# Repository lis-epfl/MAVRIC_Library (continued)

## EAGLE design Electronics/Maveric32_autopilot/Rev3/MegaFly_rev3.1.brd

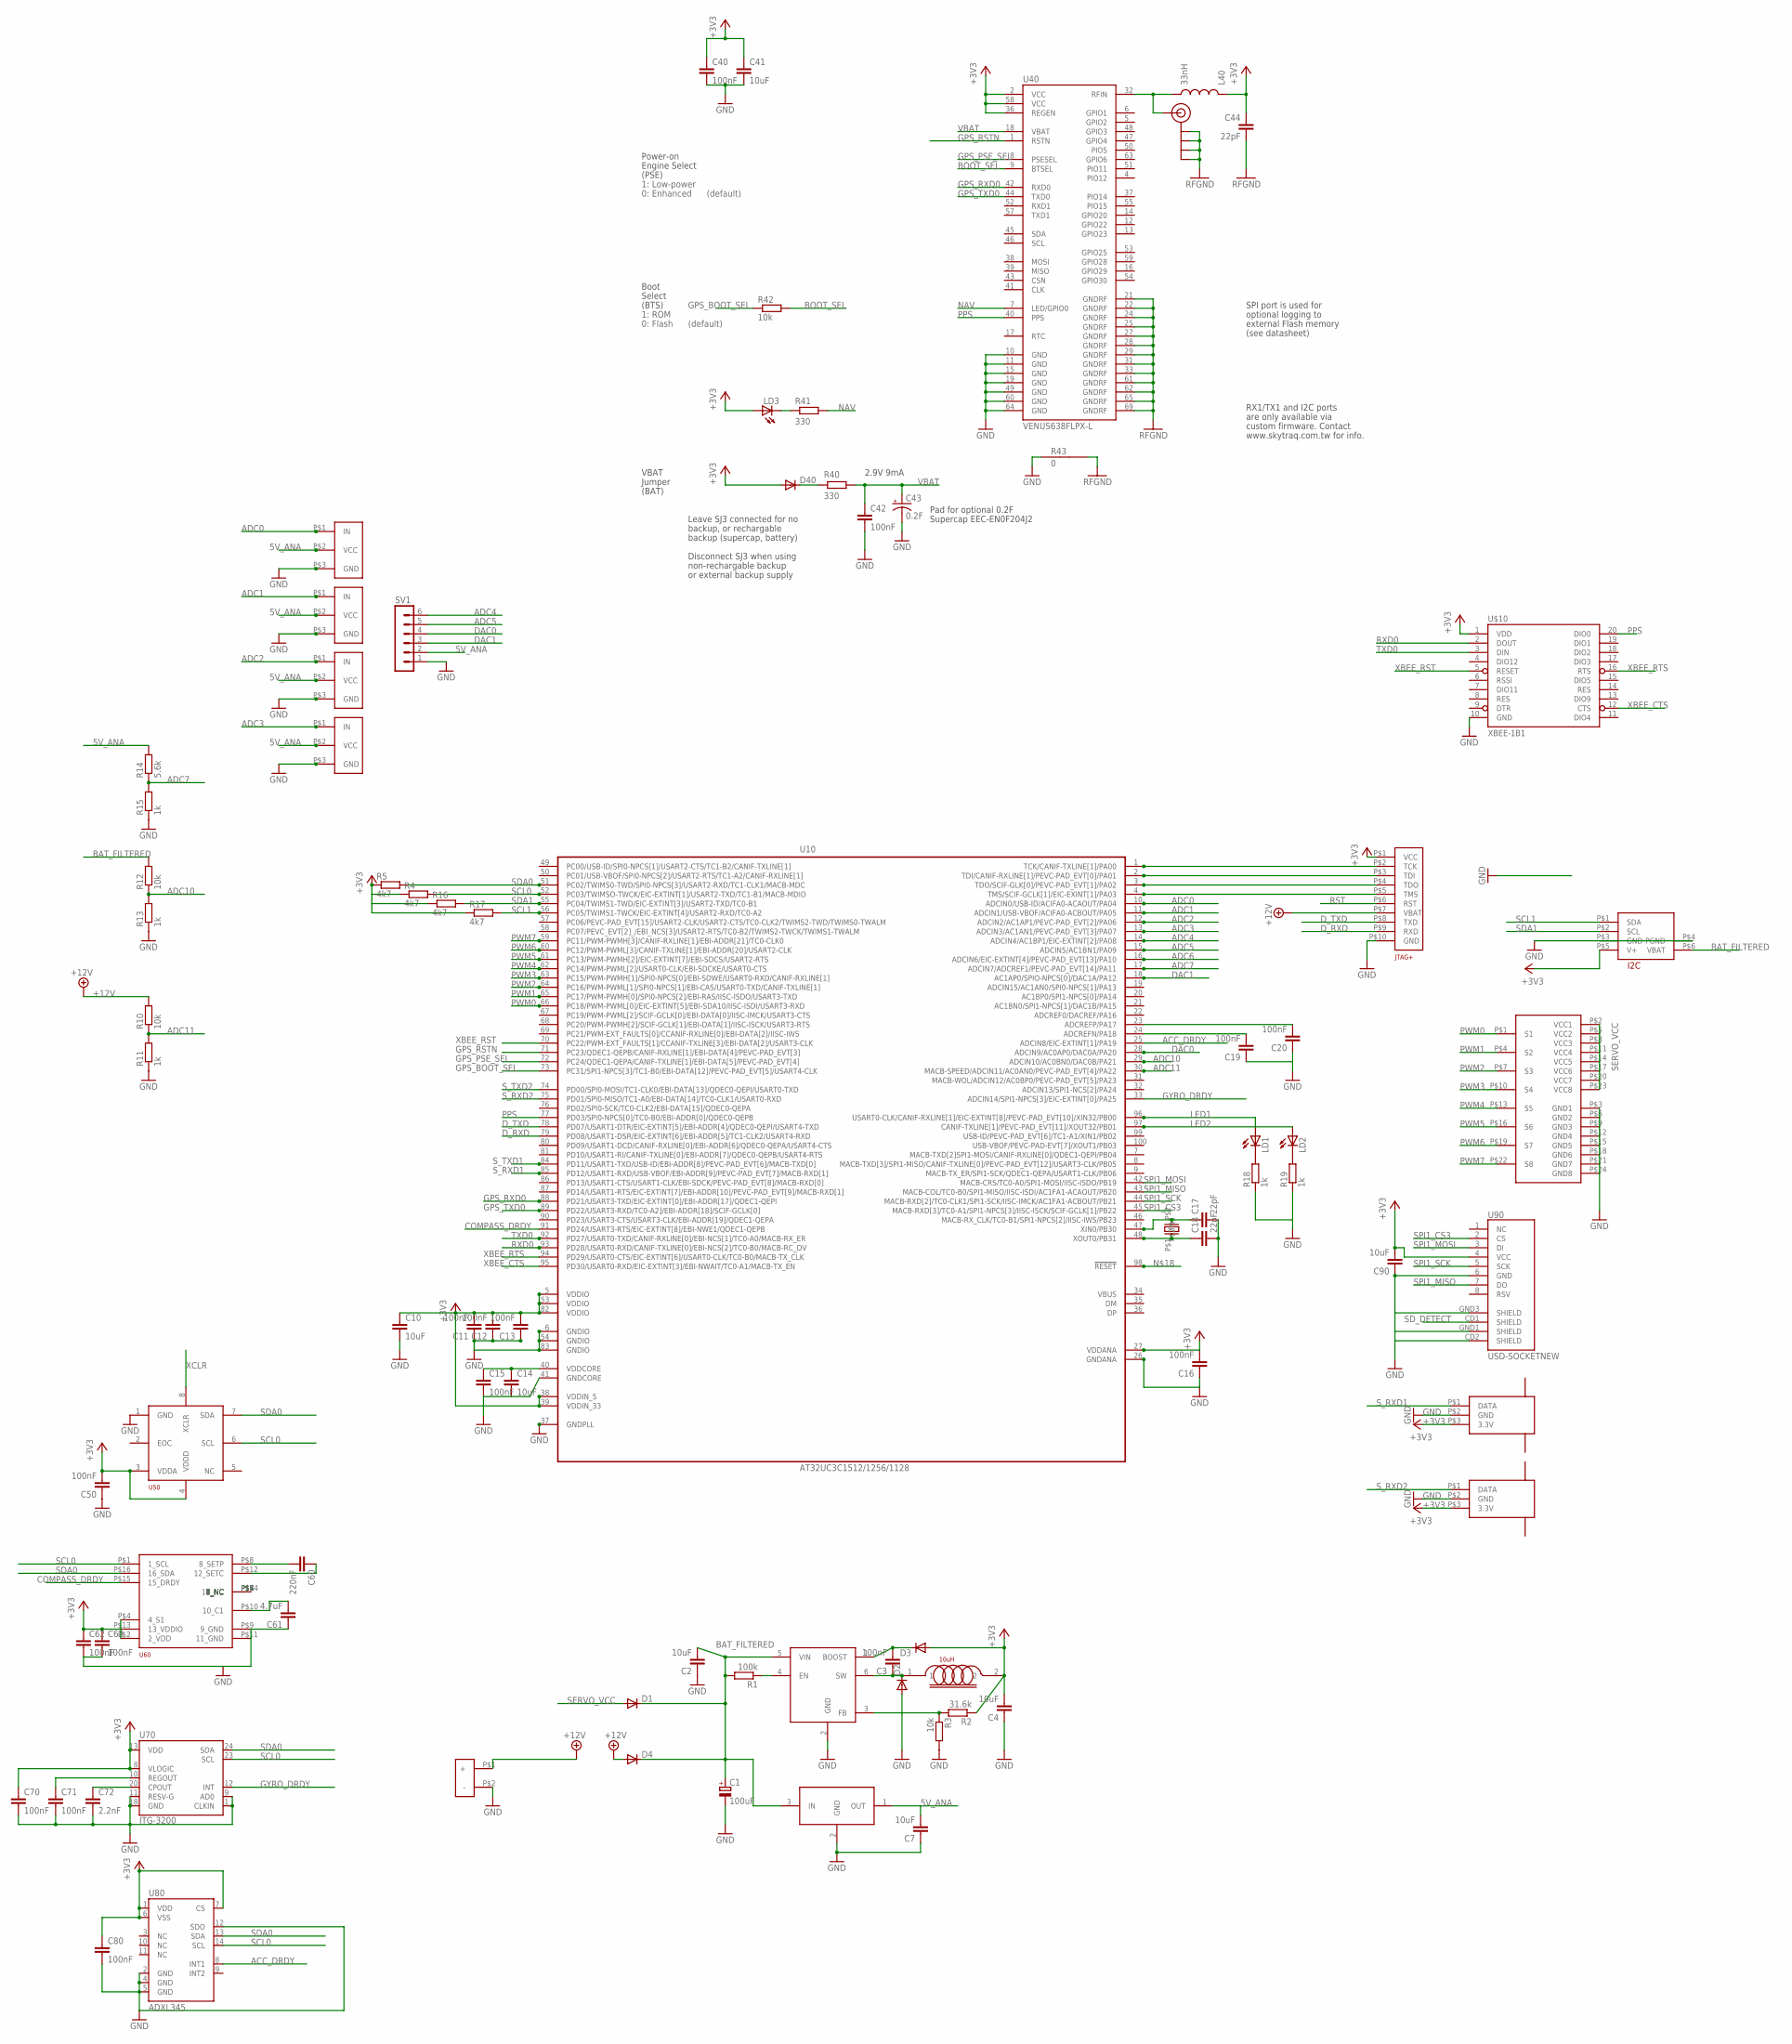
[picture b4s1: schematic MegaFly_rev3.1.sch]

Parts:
C1: 100uF; D/7343-31R
C2, C4, C7, C10, C14, C41, C90: 10uF; C0805
C3, C11, C12, C13, C15, C16, C19, C20, C40, C42, C50, C62, C63, C70, C71, C80: 100nF; C0603
C17, C18, C44: 22pF; C0402
C43: 0.2F; EN_J2
C60: 220nF; C0805
C61: 4.7uF; C0805
C72: 2.2nF; C0603
D1, D2, D3, D4, D40: DIODESOD; SOD-323
JP5: SMA_EDGE; SMA-EDGE
L1: 10uH; C1210
L40: 33nH; 0603
LD1, LD2, LD3: LEDCHIPLED_0805; CHIPLED_0805
R1: 100k; R0603
R2: 31.6k; R0603
R3, R10, R12, R42: 10k; R0603
R4, R5, R16, R17: 4k7; R0603
R11, R13, R15, R18, R19: 1k; R0603
R14: 5.6k; R0603
R40, R41: 330; R0603
R43: 0; GND-JUMP
SV1: MA06-1
U1: LM2734; SOT23-6
U2: LDO_3PINSOT89_MC78LXX; SOT89
U10: AT32UC3C1512/1256/1128; TQFP100
U40: VENUS638FLPX-L; VENUS638FLPX
U50: BMP085
U60: HMC5883L; LPCC16_0.5MM
U70: ITG-3200; QFN-24
U80: ADXL345; LGA14
U90: USD-SOCKETNEW; MICRO-SD-SOCKET-PP
U$1: AVR32_JTAG+SERIAL; MOLEX_CONNECTOR_10PINS
U$3: SERVOCONNECTOR_X8STANDARD; HEADER3X8
U$8: CRYSTAL; SMD_CRYSTAL_ABM
U$9: POWER
U$10: XBEE-1B1; XBEE-1
U$11, U$12: SPEKTRUM_RECEIVER; JST_1.5MM_3WAY
U$13, U$15, U$16, U$17: SENSOR; SERVO_COMPACT
U$18: I2C-BUS; I2C-HEADER

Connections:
5V_ANA: C7.2, R14.2, SV1.2, U2.1 (OUT), U$13.P$2 (VCC), U$15.P$2 (VCC), U$16.P$2 (VCC), U$17.P$2 (VCC)
+3V3: C4.2, C10.1, C11.2, C12.2, C13.2, C16.2, C40.1, C41.1, C44.1, C50.2, C62.1, C63.1, C70.1, C80.1, C90.2, D3.2 (A), D40.2 (A), L1.2, L40.1, LD3.A, R2.1, R4.1, R5.1, R16.1, R17.1, U10.5 (VDDIO), U10.27 (VDDANA), U10.38 (VDDIN_5), U10.39 (VDDIN_33), U10.53 (VDDIO), U10.82 (VDDIO), U40.2 (VCC), U40.36 (REGEN), U40.58 (VCC), U50.3 (VDDA), U50.4 (VDDD), U60.P$2 (2_VDD), U60.P$4 (4_S1), U60.P$13 (13_VDDIO), U70.8 (VLOGIC), U70.13 (VDD), U80.1 (VDD), U80.6 (VSS), U80.7 (CS), U90.4 (VCC), U$1.P$1 (VCC), U$10.1 (VDD), U$11.P$3 (3.3V), U$12.P$3 (3.3V), U$18.P$5 (V+)
+12V: D4.2 (A), R10.2, U$1.P$7 (VBAT), U$9.P$1 (+)
ACC_DRDY: U80.8 (INT1)
ADC0: U10.10 (ADCIN0/USB-ID/ACIFA0-ACAOUT/PA04), U$17.P$1 (IN)
ADC1: U10.11 (ADCIN1/USB-VBOF/ACIFA0-ACBOUT/PA05), U$16.P$1 (IN)
ADC2: U10.12 (ADCIN2/AC1AP1/PEVC-PAD_EVT[2]/PA06), U$13.P$1 (IN)
ADC3: U10.13 (ADCIN3/AC1AN1/PEVC-PAD_EVT[3]/PA07), U$15.P$1 (IN)
ADC4: SV1.6, U10.14 (ADCIN4/AC1BP1/EIC-EXTINT[2]/PA08)
ADC5: SV1.5, U10.15 (ADCIN5/AC1BN1/PA09)
ADC6: U10.16 (ADCIN6/EIC-EXTINT[4]/PEVC-PAD_EVT[13]/P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)
ADC7: R14.1, R15.2, U10.17 (ADCIN7/ADCREF1/PEVC-PAD_EVT[14]/PA11)
ADC10: R12.1, R13.2, U10.29 (ADCIN10/AC0BN0/DAC0B/PA21)
ADC11: R10.1, R11.2, U10.30 (MACB-SPEED/ADCIN11/AC0AN0/PEVC-PAD_EVT[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)
ANT: JP5.SIG (SIGNAL), L40.2, U40.32 (RFIN)
BAT_FILTERED: C1.+, C2.2, D1.1 (C), D4.1 (C), R1.2, R12.2, U1.5 (VIN), U2.3 (IN), U$18.P$6 (VBAT)
BOOT_SEL: R42.2, U40.9 (BTSEL)
COMPASS_DRDY: U60.P$15 (15_DRDY)
DAC0: SV1.4, U10.28 (ADCIN9/AC0AP0/DAC0A/PA20)
DAC1: SV1.3, U10.18 (AC1AP0/SPIO-NPCS[0]/DAC1A/PA12)
D_RXD: U10.79 (PD08/USART1-DSR/EIC-EXTINT[6]/EBI-ADDR[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), U$1.P$9 (RXD)
D_TXD: U10.78 (PD07/USART1-DTR/EIC-EXTINT[5]/EBI-ADDR[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), U$1.P$8 (TXD)
GND: C1.-, C2.1, C4.1, C7.1, C10.2, C11.1, C12.1, C13.1, C14.2, C15.2, C16.1, C17.2, C18.2, C19.1, C20.1, C40.2, C41.2, C42.2, C43.-, C50.1, C61.1, C62.2, C63.2, C70.2, C71.2, C72.2, C80.2, C90.1, D2.2 (A), R3.2, R11.1, R13.1, R15.1, R18.1, R19.1, R43.1, SV1.1, U1.2 (GND), U2.2 (GND), U10.6 (GNDIO), U10.26 (GNDANA), U10.37 (GNDPLL), U10.41 (GNDCORE), U10.54 (GNDIO), U10.83 (GNDIO), U40.10 (GND), U40.11 (GND), U40.15 (GND), U40.19 (GND), U40.49 (GND), U40.60 (GND), U40.64 (GND), U50.1 (GND), U60.P$9 (9_GND), U60.P$11 (11_GND), U70.1 (CLKIN), U70.9 (AD0), U70.11 (RESV-G), U70.18 (GND), U80.2 (GND), U80.4 (GND), U80.5 (GND), U80.12 (SDO), U90.6 (GND), U90.CD2 (SHIELD), U90.GND1 (SHIELD), U90.GND3 (SHIELD), U$1.P$10 (GND), U$3.P$3 (GND1), U$3.P$6 (GND2), U$3.P$9 (GND3), U$3.P$12 (GND4), U$3.P$15 (GND5), U$3.P$18 (GND6), U$3.P$21 (GND7), U$3.P$24 (GND8), U$9.P$2 (-), U$10.10 (GND), U$11.P$2 (GND), U$12.P$2 (GND), U$13.P$3 (GND), U$15.P$3 (GND), U$16.P$3 (GND), U$17.P$3 (GND), U$18.P$3 (GND), U$18.P$4 (PGND)
GPS_BOOT_SEL: R42.1, U10.73 (PC31/SPI1-NPCS[3]/TC1-B0/EBI-DATA[12]/P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)
GPS_PSE_SEL: U10.72 (PC24/QDEC1-QEPA/CANIF-TXLINE[1]/EBI-DAT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), U40.8 (PSESEL)
GPS_RSTN: U10.71 (PC23/QDEC1-QEPB/CANIF-RXLINE[1]/EBI-DAT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), U40.1 (RSTN)
GPS_RXD0: U10.88 (PD21/USART3-TXD/EIC-EXTINT[0]/EBI-ADDR[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), U40.42 (RXD0)
GPS_TXD0: U10.89 (PD22/USART3-RXD/TC0-A2]/EBI-ADDR[18]/SC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), U40.44 (TXD0)
GYRO_DRDY: U70.12 (INT)
LED1: LD1.A, U10.96 (USART0-CLK/CANIF-RXLINE[1]/EIC-EXTINT[8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)
LED2: LD2.A, U10.97 (CANIF-TXLINE[1]/PEVC-PAD_EVT[11]/XOUT32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)
unnamed: U10.4 (TMS/SCIF-GCLK[1]/EIC-EXINT[1]/PA03), U$1.P$5 (TMS)
unnamed: U10.3 (TDO/SCIF-GLK[0]/PEVC-PAD_EVT[1]/PA02), U$1.P$4 (TDO)
unnamed: C18.1, U10.48 (XOUT0/PB31), U$8.P$1
unnamed: C17.1, U10.47 (XIN0/PB30), U$8.P$2
unnamed: LD1.C, R18.2
unnamed: R1.1, U1.4 (EN)
unnamed: LD2.C, R19.2
unnamed: C3.1, D2.1 (C), L1.1, U1.6 (SW)
unnamed: R2.2, R3.1, U1.3 (FB)
unnamed: C3.2, D3.1 (C), U1.1 (BOOST)
unnamed: C72.1, U70.20 (CPOUT)
unnamed: C61.2, U60.P$10 (10_C1)
unnamed: C60.2, U60.P$8 (8_SETP)
unnamed: C60.1, U60.P$12 (12_SETC)
unnamed: C71.1, U70.10 (REGOUT)
unnamed: LD3.C, R41.1
unnamed: U10.2 (TDI/CANIF-RXLINE[1]/PEVC-PAD_EVT[0]/PA01), U$1.P$3 (TDI)
unnamed: C14.1, C15.1, U10.40 (VDDCORE)
unnamed: D40.1 (C), R40.1
unnamed: U10.1 (TCK/CANIF-TXLINE[1]/PA00), U$1.P$2 (TCK)
unnamed: C19.2, U10.24 (ADCREFN/PA18)
unnamed: C20.2, U10.23 (ADCREFP/PA17)
NAV: R41.2, U40.7 (LED/GPIO0)
PPS: U10.77 (PD03/SPI0-NPCS[0]/TC0-B0/EBI-ADDR[0]/QD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), U40.40 (PPS), U$10.20 (DIO0)
PWM0: U10.66 (PC18/PWM-PWML[0]/EIC-EXTINT[5]/EBI-SDA1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), U$3.P$1 (S1)
PWM1: U10.65 (PC17/PWM-PWMH[0]/SPI0-NPCS[2]/EBI-RAS/I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), U$3.P$4 (S2)
PWM2: U10.64 (PC16/PWM-PWML[1]/SPI0-NPCS[1]/EBI-CAS/U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), U$3.P$7 (S3)
PWM3: U10.63 (PC15/PWM-PWMH[1]/SPI0-NPCS[0]/EBI-SDWE/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), U$3.P$10 (S4)
PWM4: U10.62 (PC14/PWM-PWML[2]/USART0-CLK/EBI-SDCKE/U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), U$3.P$13 (S5)
PWM5: U10.61 (PC13/PWM-PWMH[2]/EIC-EXTINT[7]/EBI-SDCS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), U$3.P$16 (S6)
PWM6: U10.60 (PC12/PWM-PWML[3]/CANIF-TXLINE[1]/EBI-AD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), U$3.P$19 (S7)
PWM7: U10.59 (PC11/PWM-PWMH[3]/CANIF-RXLINE[1]/EBI-AD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), U$3.P$22 (S8)
RFGND: C44.2, JP5.GND@0 (GND), JP5.GND@1 (GND), JP5.GND@2 (GND), JP5.GND@3 (GND), R43.2, U40.21 (GNDRF), U40.22 (GNDRF), U40.24 (GNDRF), U40.25 (GNDRF), U40.27 (GNDRF), U40.28 (GNDRF), U40.29 (GNDRF), U40.31 (GNDRF), U40.33 (GNDRF), U40.61 (GNDRF), U40.62 (GNDRF), U40.65 (GNDRF), U40.69 (GNDRF)
RST: U$1.P$6 (RST)
RXD0: U10.93 (PD28/USART0-RXD/CANIF-TXLINE[0]/EBI-NCS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), U$10.2 (DOUT)
SCL0: R4.2, U10.52 (PC03/TWIMSO-TWCK/EIC-EXTINT[1]/USART2-T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), U50.6 (SCL), U60.P$1 (1_SCL), U70.23 (SCL), U80.14 (SCL)
SCL1: R17.2, U10.56 (PC05/TWIMS1-TWCK/EIC-EXTINT[4]/USART2-R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), U$18.P$1 (SDA)
SDA0: R5.2, U10.51 (PC02/TWIMS0-TWD/SPI0-NPCS[3]/USART2-RXD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), U50.7 (SDA), U60.P$16 (16_SDA), U70.24 (SDA), U80.13 (SDA)
SDA1: R16.2, U10.55 (PC04/TWIMS1-TWD/EIC-EXTINT[3]/USART2-TX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), U$18.P$2 (SCL)
SD_DETECT: U90.CD1 (SHIELD)
SERVO_VCC: D1.2 (A), U$3.P$2 (VCC1), U$3.P$5 (VCC2), U$3.P$8 (VCC3), U$3.P$11 (VCC4), U$3.P$14 (VCC5), U$3.P$17 (VCC6), U$3.P$20 (VCC7), U$3.P$23 (VCC8)
SPI1_CS3: U10.45 (MACB-RXD[3]/TC0-A1/SPI1-NPCS[3]/IISC-IS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), U90.2 (CS)
SPI1_MISO: U10.43 (MACB-COL/TC0-B0/SPI1-MISO/IISC-ISDI/AC1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), U90.7 (DO)
SPI1_MOSI: U10.42 (MACB-CRS/TC0-A0/SPI1-MOSI/IISC-ISDO/PB19), U90.3 (DI)
SPI1_SCK: U10.44 (MACB-RXD[2]/TC0-CLK1/SPI1-SCK/IISC-IMCK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), U90.5 (SCK)
S_RXD1: U10.85 (PD12/USART1-RXD/USB-VBOF/EBI-ADDR[9]/PE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), U$11.P$1 (DATA)
S_RXD2: U10.75 (PD01/SPI0-MISO/TC1-A0/EBI-DATA[14]/TC0-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), U$12.P$1 (DATA)
S_TXD1: U10.84 (PD11/USART1-TXD/USB-ID/EBI-ADDR[8]/PEVC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)
S_TXD2: U10.74 (PD00/SPI0-MOSI/TC1-CLK0/EBI-DATA[13]/QD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)
TXD0: U10.92 (PD27/USART0-TXD/CANIF-RXLINE[0]/EBI-NCS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), U$10.3 (DIN)
VBAT: C42.1, C43.+, R40.2, U40.18 (VBAT)
XBEE_CTS: U10.95 (PD30/USART0-RXD/EIC-EXTINT[3]/EBI-NWAIT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), U$10.12 (CTS)
XBEE_RST: U10.70 (PC22/PWM-EXT_FAULTS[1]/CCANIF-TXLINE[3]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), U$10.5 (RESET)
XBEE_RTS: U10.94 (PD29/USART0-CTS/EIC-EXTINT[6]/USART0-CL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), U$10.16 (RTS)
XCLR: U50.8 (XCLR)

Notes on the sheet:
RFGND
1: Low-power
0: Enhanced
0: Flash
1: ROM
(default)
Supercap EEC-EN0F204J2
Pad for optional 0.2F
2.9V 9mA
RX1/TX1 and I2C ports
are only available via
SPI port is used for
optional logging to
external Flash memory
(see datasheet)
custom firmware. Contact
www.skytraq.com.tw for info.
Power-on
Engine Select
Boot
Select
(PSE)
(BTS)
VBAT
Jumper
(BAT)
Leave SJ3 connected for no
backup, or rechargable
backup (supercap, battery)
Disconnect SJ3 when using
non-rechargable backup
or external backup supply

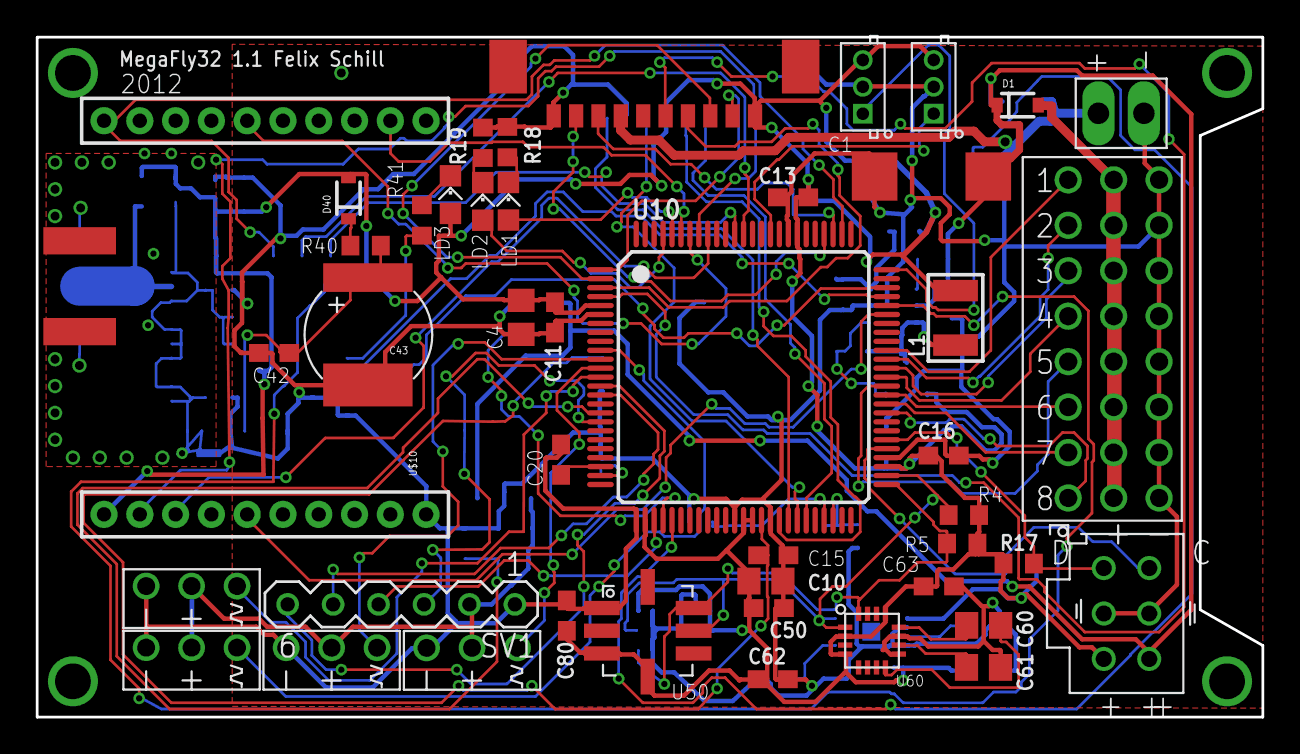
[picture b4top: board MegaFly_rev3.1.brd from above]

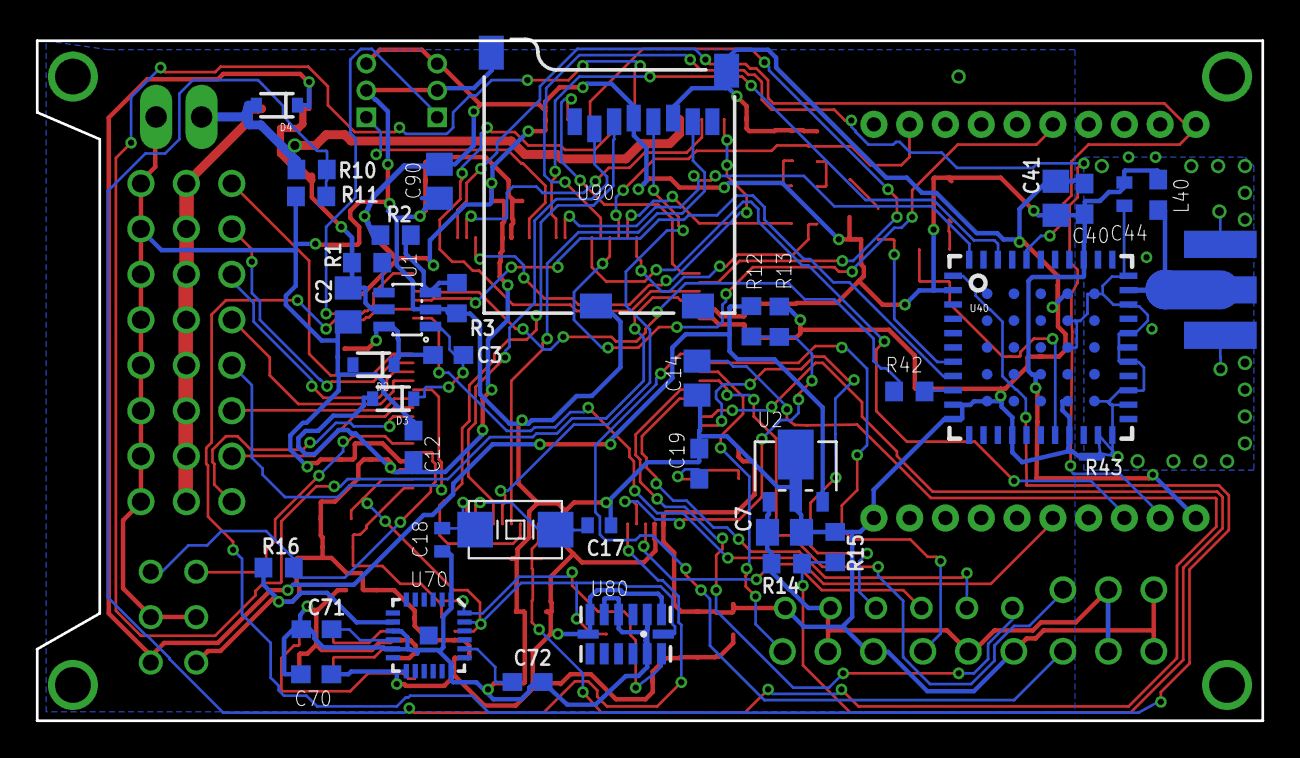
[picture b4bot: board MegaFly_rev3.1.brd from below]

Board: 2 copper layers, 68.5 x 38.0 mm, 83 parts (39 on the bottom side), 77 nets.

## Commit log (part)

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2016-09-13 move include *.hpp out of extern C
2016-09-13 update documentation
2016-09-13 Move definition of conf_t inside Data_logging
2016-09-13 move *.hpp out of extern C
2016-09-13 Mission Handler working with stabilisation copter (yaw still strange)
2016-09-13 Fix include path
2016-09-13 Add extern C
2016-09-13 added commented line for dronedome
2016-09-14 LEQuad_dronedome: moved call of gps_mocap_.init() and ahrs_ekf_mocap_.init() to init()
2016-09-15 Waypoint_handler: changed callbacks to listen to messages for target_component 50 for compatibility with DroneKit
2016-09-15 Disable magnetometer
2016-09-15 Fix cimpilation
2016-09-15 added interrupt
2016-09-15 - Improved reliability and readability
2016-09-15 Fix compile issues after merge
2016-09-16 Rename fields of Mavlink_communication::conf_t
2016-09-16 Add compiler flags on sample projects, lots of warnings
2016-09-16 Move chibios project to folder untested
2016-09-16 Added yaw to hold position
2016-09-16 Remove mallocs, add ChibiOS/HAL (#326)
    * Rename Bmp085 -> Barometer_BMP085 and remove most members from barometer interface
    * Add skeleton of ms5611 driver
    * Set 0 interval for usb cdc
    * Make sure we use FPU
    * Add i2c and barometer to sparky
    * Test setup, TODO uncomment protected keyword in LEQuad
2016-09-19 rfm22b configuration according to Taulabs (WIP). Configuration done, Receiving almost done
2016-09-20 Added necessary file to rules
2016-09-20 LEQuad: Moved init_* calls from constructor to dedicated init() function (#329)
    * LEQuad: Moved init_* calls from constructor to dedicated init() function
    This allows to override init_* functions from child classes
    * LEQuad_dronedome: moved call of gps_mocap_.init() and ahrs_ekf_mocap_.init() to init()
2016-09-21 Removed heading command from standby mode
2016-09-21 Added mission enum to switch case
2016-09-21 Removed Mission_planner::is_arrived()
2016-09-21 Rename boolean to is_XXX
2016-09-21 Add const
2016-09-21 Remove camelCase
2016-09-22 Renamed callbacks to mavlink commands to match command name in waypoint_handler
2016-09-22 Remove dubious piece of code and add comment
2016-09-22 Changed Mission_handler::update() return to an enum
2016-09-22 Position_estimation: removed resetting of origin when arming
    - Removed resetting of origin and local_position estimation from reset_origin_position
    - Renamed reset_origin_position to reset_velocity_altitude (since it does not reset origin anymore)
    - Renamed init_gps_position to is_gps_pos_initialized_
2016-09-22 Removed position_estimation_telemetry
    Since downward telemetry was moved to ins_telemetry, only set_new_home_position remained, which changes the origin and hence is dangerous and should not be called from groundstation
    (If we allow change of origin, the message SET_GPS_GLOBAL_ORIGIN should be used instead)
2016-09-22 INS: changed access to INS::origin_ to private and added protected function set_origin
    This allows to easily identify places where the origin is changed and would allow to add test before changing
2016-09-22 Added time recording for waypoints list received
2016-09-22 Fixed order of landing handler update function to prevent accidental auto-takeoff after rearming
2016-09-22 Added go home callback
2016-09-22 Fix compilation of Barometer_MS5611
2016-09-22 Update libopencm3
2016-09-22 INS_telemetry: changed function names and added ins_telemetry_init to LEQuad::init_position_estimation()
2016-09-23 Reduced checks in waypoint communication
2016-09-23 Rebuild doc at b3b1bd32d5ea67fe53f0b3866194a7c5c9367651
2016-09-23 Removed waypoint initialization
2016-09-23 Remove altitude bias in Barometer interface, add pressure at sea level and formulas
2016-09-23 Send pressure through telemetry
2016-09-23 Oops, fix altitude calculation in bmp driver
2016-09-23 Fixed receiving 0 waypoint count case
2016-09-23 Rate_controller + Position_controller: bug fix
2016-09-23 Revert mavlink submodule
2016-09-23 Removed waiting at waypoint
2016-09-23 Removed navigation.start_wpt_time_
2016-09-23 add ref
2016-09-23 Revert mavlin ksubmodule
2016-09-23 Use imu config from config file
2016-09-23 Fix alignment + comments
2016-09-23 Remove warnings
2016-09-23 Rebuild doc at 931845616a7c53324a3e7fe54b7da050bc4fe5f9
2016-09-26 Added rate control to on ground handler
2016-09-26 Added yaw function to ahrs struct
2016-09-26 Make sure task function pointer and function argument are of compatible type
2016-09-26 Message handler: make sure task function pointer and function argument are of compatible type
2016-09-26 Re-add commented msg callback
2016-09-27 Manual_control: changed get_attitude_command
2016-09-27 Joystick: changed default config for yaw scale to be adapted for get_attitude_command
2016-09-27 Rebuild doc at cd15f5fbb25a0206cc71d4d098c75a1cf05088d9
2016-09-27 add missing init
2016-09-27 Added mavlink land on tag enum
2016-09-27 Changed land on tag callback prints
2016-09-27 - Renamed appropriately
2016-09-27 - Configured for working with UART4
2016-09-27 - All dummy files..
2016-09-28 Moved descent to ground altitude to config
2016-09-28 Position_controller: fixed bug: setting to xyz mode on update_cascade
2016-09-28 Added check for empty task list in scheduler
2016-09-28 Fixed compiler issues
2016-09-28 Made range for switch to desc2gnd a config param
2016-09-28 Changed params
2016-09-28 Rebuild doc at 68ff135415871ba20eec0815cd3133709ac956ea
2016-09-29 Fixed communication object for tag callback
2016-09-30 Rearranged lpf
2016-10-13 Remove .dep folder from git
2016-10-13 Quickfix/dep folder (#338)
    * Remove .dep folder from git
    * Add .dep to gitignore
2016-10-13 Add servo mix using matrix (#339)
2016-10-13 Fix after merge
2016-10-13 Impl some comments
2016-10-13 Example in doc
2016-10-13 Modified function naming for clang compilation
2016-10-13 Rename also altitude_from_pressure, rename getter for pressure at sea level, revert git hash length
2016-10-13 Kalman filter for position estimation (#332)
    * Add skeleton for position/velocity kalman (linear)
    * Add px4flow to kalman position estimation
    * Add driver for stock px4Flow connected using i2c
    * Add px4flow to project
    * Fix linux project
    * Add method to get buffer element without removing it
2016-10-13 Rebuild doc at dc28b7498c6578792ae96374f601fa6322885009
2016-10-13 Rebuild doc at 3a76e68c1df97e3be940f8f558d4eb2e82cd7c6f
2016-10-14 Rebuild doc at f6f1d6e663d5628278456b38852a17fb40ae2aad
2016-10-14 Mission handler (#331)
    * Use X Y Z instead of 0, 1, 2
    * Use default origin location in constants.hpp
    * Style
    * Use Z instead of 2
    * Style
    * Fix include
2016-10-20 LEQuad dronedome by default
2016-10-20 Add update task and telemetry for optic flow sensor
2016-10-20 adaptation for dronedome
2016-10-20 Add parameter for sigma flow
2016-10-20 Force ins kf init after first fix
2016-10-20 Rebuild doc at de9486da99fd9fe4c1ec55e0643abc29ead6c824
2016-10-21 Add Flow sensor to position estimation, split corrections in methods, clean unused members
2016-10-21 Update few file headers
2016-10-24 Folder reorganisation (#344)
    * Add Flow sensor to position estimation, split corrections in methods, clean unused members
    * Renamed Position_estimation -> INS_complementary
    * Update few file headers
    * Create folders for manual control, status, and navigation
2016-10-24 Add gps hub to deal with redundant gps
2016-10-24 Gps hub (#345)
    * Add Flow sensor to position estimation, split corrections in methods, clean unused members
    * Renamed Position_estimation -> INS_complementary
    * Update few file headers
    * Add gps hub to deal with redundant gps
    * Use gps hub in INS_complementary with different gains based on fix type
    * Fix syntax for avr32-gcc
2016-10-24 Add geofence interface + implementation using cylinder
2016-10-24 Rebuild doc at b61adde63854bd47c174ee5b8da161049489b05b
2016-10-25 Clean control_command.h
2016-10-25 Mega controller cleaning (ongoing)
2016-10-26 Add trim, min and max values to Servo_mix_matrix
2016-10-28 Move LEQuad to dedicated folder
2016-10-28 Add lequad to rules_common.mk (#347)
    * Add lequad to rules_common.mk
    * Move LEQuad to dedicated folder
    * Few adds from merk branch
2016-10-28 Fix GPS gain in RTK mode
2016-10-28 Print git tag of Library during compilation
2016-10-29 Increased serial rx buffer of avr32 from 1024 to 2048
2016-10-29 Rebuild doc at 651e3bbd1301705584b89178d3401afcf4ab9acd
2016-11-03 Init mav in main_sparky
2016-11-03 Use dummy sensors
2016-11-03 Face north
2016-11-03 Updates in GSM
2016-11-08 misc
2016-11-25 Sonar i2cxl, check that i2c comm succedded before using data
2016-11-25 Avoid modulo 0 when waypoint count is 0
2016-11-25 Use fixed heading in navigation, switch waypoint when speed is low
2016-11-25 Single entry point for control commands (#351)
    * Set autopilot type to generic
    * Clean control_command.h
    * Mega controller cleaning
    * Fix syntax for avr32-gcc
    * Update
    * Remove duplicated code between joystick and remote
2016-11-29 Move old servos mix to unsupported folder
2016-11-29 Fix syntax for avr32
2016-11-29 Rebuild doc at 471247f612fcdf3895c87b6979e65a06faff0475
2016-11-29 Rebuild doc at eb1b622764e08250534bfe0f66c3e3cdccaa51c7
2016-11-29 Mav class (#354)
    * Started to add a base MAV class (hack)
    * Fix syntax for avr32
2016-11-29 Fix yaw signs in flight_controller_hexacopter
2016-11-29 Rebuild doc at 12165a83b4795d88df566be0f4ce6227d0ef4fb6
2016-11-29 Rebuild doc at 2a5dfab89d7df45aea6bd7f5918c3c3ec8e9dc27
2016-11-30 Use dronedome config in sample projects
2016-11-30 Add anti windup on pid controller
2016-11-30 Increase nav speed threshold to 1m/s
2016-12-01 Corrected next execution time of periodic relative scheduler timing mode
2016-12-01 Corrected next execution time of periodic relative scheduler timing mode (#357)
2016-12-01 Velocity controller holonomic (#358)
    * Rename Mav_mode GPS_NAV -> AUTO
    * Use dronedome config in sample projects
    * Add parameters for AHRS
    * Add anti windup on pid controller
    * Add cruise speed and cruise dist to distance controller with ramp up and down accelerations
    * Velocity_copter: use axis/angle representation and compensate thrust for bank angle
2016-12-01 Fix rate mode in main task
2016-12-01 Add pid getters and PID parameters in LEQuad
2016-12-01 Sparky lequad (#360)
    * Add pid getters and PID parameters in LEQuad
    * Use real sensors in sparjy sample project
2016-12-01 Split quadcopter controller into files, put them in separate folder
2016-12-01 Flight controller hexhog (#361)
    * Split quadcopter controller into files, put them in separate folder
    * Add flight controller for hexhog
2016-12-02 Rotate accel_vector to body frame
2016-12-02 Add doc
2016-12-02 Rebuild doc at 6e6af824077bdd148d9a64749f6937b18a7c9eb8
2016-12-05 Add configuration for control frame in Velocity_controller (#363)
2016-12-05 minor changes
2016-12-06 Add integrator to compensate constant lateral thrust
2016-12-12 Fix param name length
2016-12-12 Add methods for ins corrections
2016-12-12 Add parameters to custom ins filter (to remove)
2016-12-13 Add interface for PX4Flow, impl for i2c and serial
2016-12-13 Configure megafly for 115k uart3
2016-12-13 Cosmetics
2017-01-03 changed stuff for closed-loop exp
2017-01-26 Rebuild doc at 4d688a53209013d8f91f11e93debd7b8a6817807
2017-02-02 Reformulate holonomic accel thres
2017-02-02 Rebuild doc at 56281851da7541d5c1199490a8621d7f18482be1
2017-03-23 Ublox: FIX_ERR when not connected
2017-03-24 Add manual control method to flight_controller, fix trim in fixed wing flight controller, increase manual rate scales for wings
2017-03-24 Roll/pitch gains and manual scales
2017-03-27 Add flag to disable geofence
2017-03-31 AHRS_EKF: by default use only horizontal (2d) magnetic field
2017-03-31 Add estimation of baro bias
2017-04-03 Remove freertos submodule
